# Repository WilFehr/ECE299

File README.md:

# ECE299

This repo contains all relavent files used to created the final deliverable for the ECE299 radio + alarm clock project.

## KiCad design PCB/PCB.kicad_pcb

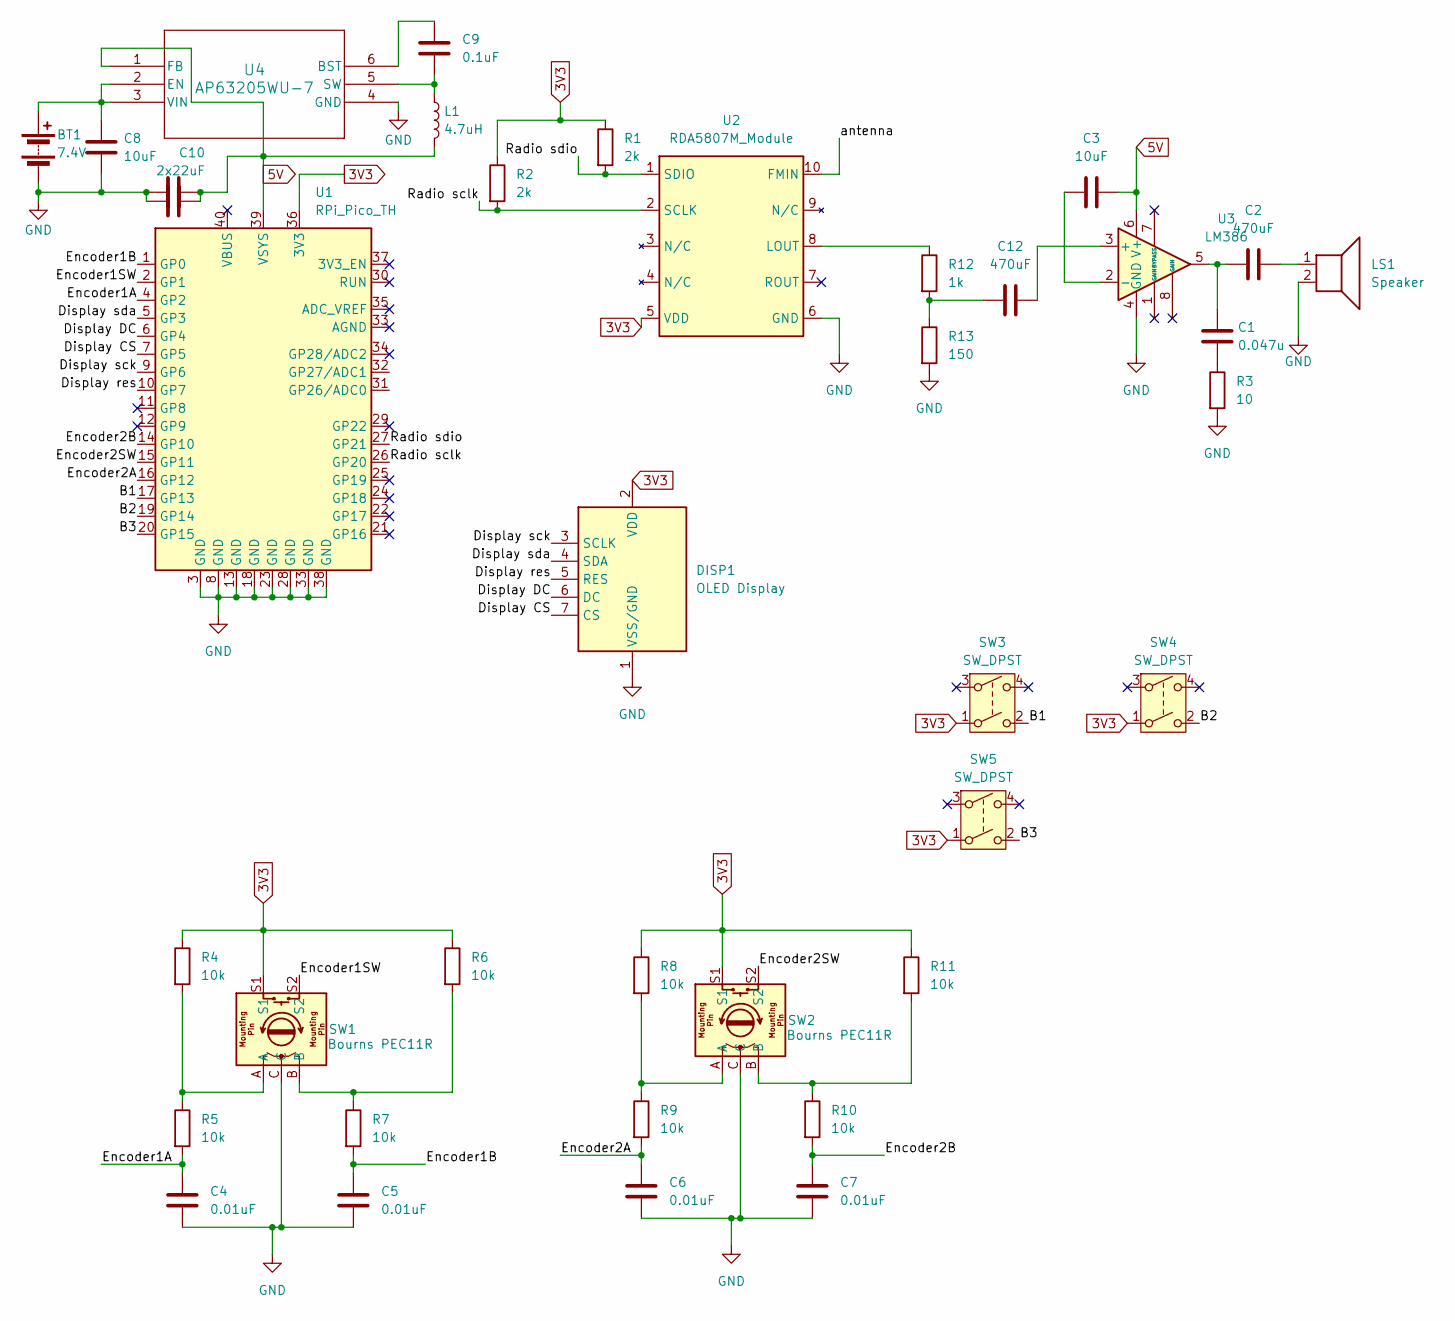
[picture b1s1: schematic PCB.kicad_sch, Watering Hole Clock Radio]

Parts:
BT1: 7.4V; THT Battery Connection
C1: 0.047u; C_Disc_D6.0mm_W2.5mm_P5.00mm
C2, C12: 470uF; C_Radial_D6.3mm_H11.0mm_P2.50mm
C3: 10uF; C_Radial_D5.0mm_H11.0mm_P2.00mm
C4, C5, C6, C7: 0.01uF; C_Disc_D6.0mm_W2.5mm_P5.00mm
C8: 10uF; C_1206_3216Metric
C9: 0.1uF; C_0805_2012Metric
C10, C11: 2x22uF; C_1206_3216Metric
DISP1: OLED Display; 1727065
L1: 4.7uH; L_Cenker_CKCS201610
LS1: Speaker; 691137710002
R1, R2: 2k; R_Axial_DIN0207_L6.3mm_D2.5mm_P7.62mm_Horizontal
R3: 10; R_Axial_DIN0207_L6.3mm_D2.5mm_P7.62mm_Horizontal
R4, R5, R6, R7, R8, R9, R10, R11: 10k; R_Axial_DIN0207_L6.3mm_D2.5mm_P7.62mm_Horizontal
R12: 1k; R_Axial_DIN0207_L6.3mm_D2.5mm_P7.62mm_Horizontal
R13: 150; R_Axial_DIN0207_L6.3mm_D2.5mm_P7.62mm_Horizontal
SW1, SW2: Bourns PEC11R; PHOENIX_1935190
SW3, SW4: SW_DPST; 691137710002
SW5: SW_DPST; SW_PUSH_6mm_H7.3mm
U1: RPi_Pico_TH
U2: RDA5807M_Module; RDA5807M_Module_TH
U3: LM386; DIP794W45P254L959H508Q8
U4: AP63205WU-7; SOIC_05WU-7_DIO

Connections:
3V3: DISP1.2 (VDD), R1.1, R2.1, R4.1, R6.1, R8.1, R11.1, SW1.S1, SW2.S1, SW3.1, SW4.1, SW5.1, U1.36 (3V3), U2.5 (VDD)
5V: C3.2, C10.2, C11.2, L1.2, U1.39 (VSYS), U3.6 (V+), U4.1 (FB)
/B1: SW3.2, U1.17 (GP13)
/B2: SW4.2, U1.19 (GP14)
/B3: SW5.2, U1.20 (GP15)
/Display CS: DISP1.7 (CS), U1.7 (GP5)
/Display DC: DISP1.6 (DC), U1.6 (GP4)
/Display res: DISP1.5 (RES), U1.10 (GP7)
/Display sck: DISP1.3 (SCLK), U1.9 (GP6)
/Display sda: DISP1.4 (SDA), U1.5 (GP3)
/Encoder1A: C4.1, R5.2, U1.4 (GP2)
/Encoder1B: C5.1, R7.2, U1.1 (GP0)
/Encoder1SW: SW1.S2, U1.2 (GP1)
/Encoder2A: C6.1, R9.2, U1.16 (GP12)
/Encoder2B: C7.1, R10.2, U1.14 (GP10)
/Encoder2SW: SW2.S2, U1.15 (GP11)
/Radio sclk: R2.2, U1.26 (GP20), U2.2 (SCLK)
/Radio sdio: R1.2, U1.27 (GP21), U2.1 (SDIO)
/antenna: U2.10 (FMIN)
GND: BT1.2 (-), C4.2, C5.2, C6.2, C7.2, C8.2, C10.1, C11.1, DISP1.1 (VSS/GND), LS1.2, R3.2, R13.2, SW1.C, SW2.C, U1.3 (GND), U1.8 (GND), U1.13 (GND), U1.18 (GND), U1.23 (GND), U1.28 (GND), U1.33 (GND), U1.38 (GND), U2.6 (GND), U3.4 (GND), U4.4 (GND)
unnamed: BT1.1 (+), C8.1, U4.2 (EN), U4.3 (VIN)
unnamed: C1.1, C2.1, U3.5
unnamed: C1.2, R3.1
unnamed: C2.2, LS1.1
unnamed: C12.1, R12.2, R13.1
unnamed: R4.2, R5.1, SW1.A
unnamed: R6.2, R7.1, SW1.B
unnamed: R8.2, R9.1, SW2.A
unnamed: R10.1, R11.2, SW2.B
unnamed: R12.1, U2.8 (LOUT)
unnamed: C12.2, U3.3 (+)
unnamed: C3.1, U3.2 (-)
unnamed: C9.1, U4.6 (BST)
unnamed: C9.2, L1.1, U4.5 (SW)

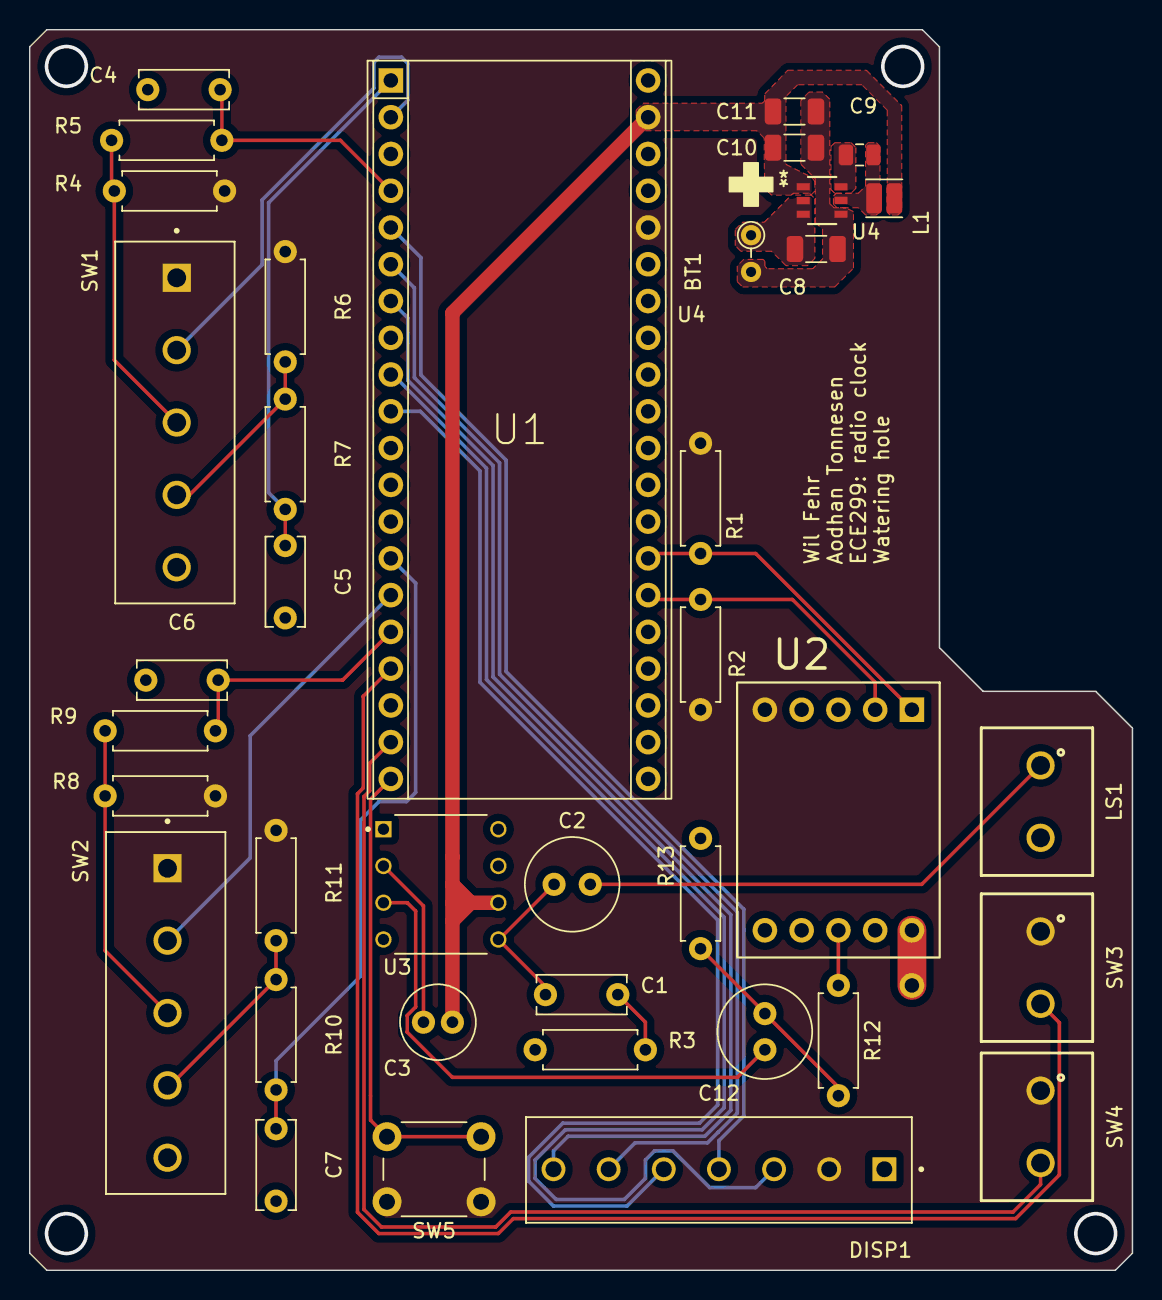
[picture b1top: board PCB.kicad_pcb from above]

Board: 2 copper layers, 76.2 x 85.7 mm, 38 parts (0 on the bottom side), 33 nets.

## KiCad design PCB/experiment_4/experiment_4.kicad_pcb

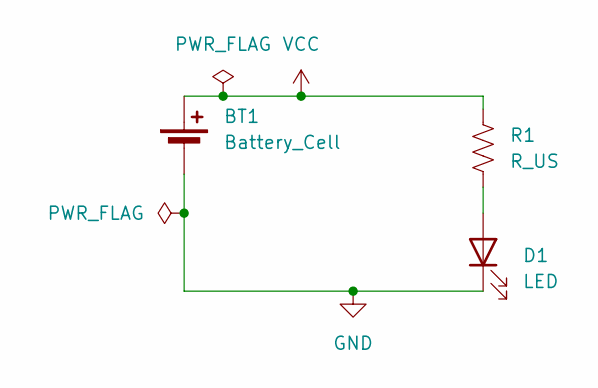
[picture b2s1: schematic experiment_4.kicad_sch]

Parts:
BT1: Battery_Cell; BatteryHolder_Keystone_1060_1x2032
D1: LED; LED_D5.0mm
R1: R_US; R_Axial_DIN0309_L9.0mm_D3.2mm_P12.70mm_Horizontal

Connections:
GND: BT1.2 (-), D1.1 (K)
unnamed: D1.2 (A), R1.2
VCC: BT1.1 (+), R1.1

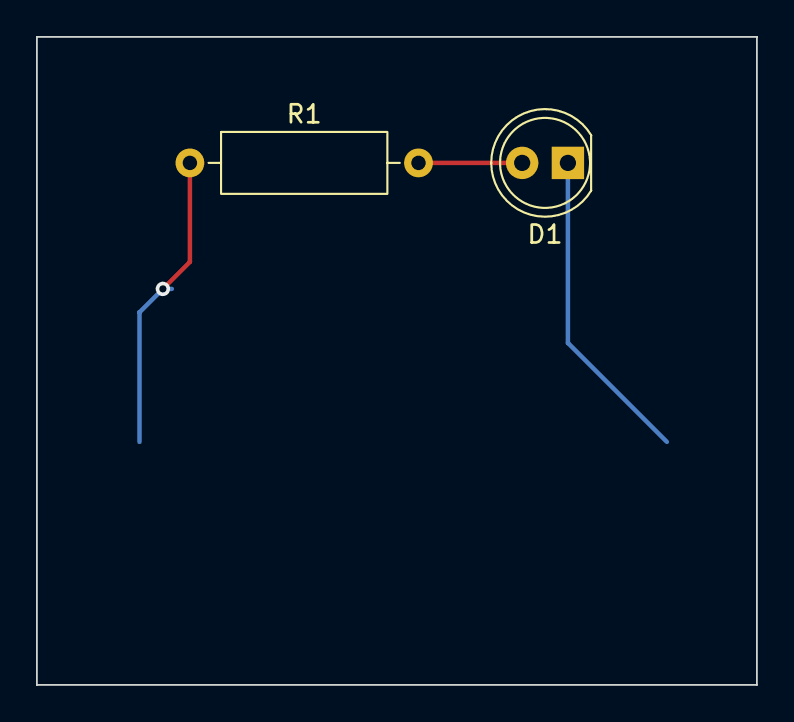
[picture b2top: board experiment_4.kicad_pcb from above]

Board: 2 copper layers, 40.0 x 36.0 mm, 3 parts (1 on the bottom side), 3 nets.

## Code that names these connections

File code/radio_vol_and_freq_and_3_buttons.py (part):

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#
# initialize encoders
#
Encoder1A = Pin( 2, Pin.IN )
Encoder1B = Pin( 0, Pin.IN )
Encoder2A = Pin(10, Pin.IN )
Encoder2B = Pin(12, Pin.IN )

#buttons
Encoder1sw = Pin( 1, Pin.IN, Pin.PULL_DOWN )
Encoder2sw = Pin(11, Pin.IN, Pin.PULL_DOWN )
Button1 = Pin( 13, Pin.IN, Pin.PULL_DOWN )
Button2 = Pin( 14, Pin.IN, Pin.PULL_DOWN )
ButtonTop = Pin(15, Pin.IN, Pin.PULL_DOWN )
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# Enable interrupt detection for both rising and falling edges of both signals
#

Encoder1A.irq( handler= Encoder1AInterrupt, trigger=Pin.IRQ_FALLING | Pin.IRQ_RISING, hard=True )
Encoder1B.irq( handler= Encoder1BInterrupt, trigger=Pin.IRQ_FALLING | Pin.IRQ_RISING, hard=True )
Encoder2A.irq( handler= Encoder2AInterrupt, trigger=Pin.IRQ_FALLING | Pin.IRQ_RISING, hard=True )
Encoder2B.irq( handler= Encoder2BInterrupt, trigger=Pin.IRQ_FALLING | Pin.IRQ_RISING, hard=True )

Encoder1sw.irq( trigger=Pin.IRQ_RISING, handler = Encoder1sw_handler)
Encoder2sw.irq( trigger=Pin.IRQ_RISING, handler = Encoder2sw_handler )
Button1.irq( trigger=Pin.IRQ_RISING, handler = Button1_handler )
Button2.irq( trigger=Pin.IRQ_RISING, handler = Button2_handler)
ButtonTop.irq( trigger=Pin.IRQ_RISING, handler = ButtonTop_handler)
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
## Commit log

2025-05-21 test code
2025-06-04 making some files
2025-06-17 test and lab code
    for display, interrupts, radio, and encoder
2025-06-21 kicad lab experiment and initial draft of schematic
2025-06-21 finished rev 0 of circuit schematic
2025-06-24 Initial look-over
    Added footprint for LM386. We will need to decide footprints for resistors, capacitors, etc.
    Any two legged through hole components can probably use the same footprint, but some components might be surface mount.
2025-06-24 Added footprint to OLED
    added 7pin screw terminal footprint to oled. Could not find OLED footprint so with this design we will just wire from OLED to screw terminal block.
2025-06-24 Added voltage regulator and battery
2025-06-24 More fiddling
2025-06-26 Footprint work
    Didn't get the regions correct, maybe they will be fixed.
2025-06-26 lab 5 tutorial
2025-06-26 PCB design #1
2025-06-27 updated code with correct pin outs
2025-06-28 updated schematic
2025-06-28 updated footprints
2025-06-28 corrected pico pin outs
2025-06-30 Updated PCB
    PCB updated to reflect new footprints and corrected connections.
2025-07-01 reverted to older sch file
    there were stashed changes that made it impossible to open the file. this may also affect the applied libraries and the pcb file
2025-07-02 Updated PCB
    PCB updated to have mounting holes, proper shape, etc.
2025-07-03 changed sw5 footprint to button footprint
2025-07-08 Updated SW5 footprint
2025-07-09 pcb manufacturing and early housing designs
    made gerber
    add names to PCB layout
    started housing designs
2025-07-09 pcb autosaves
    i forgor the diminsions that I added to the pcb
2025-07-09 some solid works parts
    housing base
    housing lid
    button extenders
2025-07-10 solid works and some code
2025-07-16 2 encoder test code
    make display info fit
2025-07-16 fonts
    fonts and some test code
2025-07-17 radio test stuff
    modified volume and freq control to control with the encoders
    added radio module datasheet
2025-07-17 change frequency to float
2025-07-29 code and some stl
2025-07-30 magnet holder
    5.3mm diameter, 5.2mm tall
2025-07-30 few stls and adding test code for the buttons
2025-08-02 housing cad and stls
